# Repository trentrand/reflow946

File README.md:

# Reflow946

> **Fork notice** — This is a modified version of [Reflow946](https://github.com/DurandA/reflow946)
> by Arnaud Durand, licensed under the [Creative Commons Attribution 4.0 International
> license](LICENSE) (CC BY 4.0). See *Modifications* below for what changed.

The Reflow946 is a Bluetooth LE temperature controller for the 946C electronic hot plate. Using this controller, a reflow profile can be programmed from your web browser using the [Web Bluetooth](https://webbluetoothcg.github.io/web-bluetooth/) API. You can use preset profiles (e.g. for lead-free or leaded soldering) or create a custom profile for a perfect cheese fondue. 🫕

The controller board is intended to replace the original controller board. It is **only compatible with the 3 buttons variant** pictured above (see this [teardown](https://youtu.be/Gv2sRJ9y_Ok)). Please send a PR if you adapted the design to a new variant.

## Hardware

The controller is based on a ESP32 module with an IPEX antenna. Since the metal case acts as a Faraday cage, the BLE signal can be improved by taping an antenna outside of the case.

### Front

### Back

## Status

- [x] Temperature control
  - [x] Temperature control using the front panel
  - [x] [BLE GATT service](https://github.com/DurandA/reflow946-firmware/wiki/GATT-Services) for temperature control
- [x] Reflow profile programming
  - [x] [BLE GATT service](https://github.com/DurandA/reflow946-firmware/wiki/GATT-Services) for reflow profiles
  - [x] [Web Bluetooth application](https://duranda.github.io/reflow946/)

## Modifications

Changes by Trent Rand (Randware), relative to upstream rev 1.2:

- Pathfinder revision (rev 2): 3-digit 7-segment display (`DS1`) replaced by a
  1.47" IPS TFT (ST7789V3, 172x320) with two parallel interfaces:
  `J6` FH12-8S-0.5SH FPC connector (v2 mounting path) and `J9` 2.54mm breakout
  header (bench bring-up). Signals ride the former segment-drive GPIOs:
  BL=dp(IO5) CS=f(IO23) DC=d(IO16) RES=g(IO13) SDA=c(IO19) SCL=d2(IO18).
  One display may be attached at a time (shared bus).
- Second MAX31855KASA (`U6`) with screw terminal `J8` (`EXT_TC`) for top-of-PCB
  thermocouple profiling; shares CLK/MISO with the primary sensor, CS on IO4.
- Breakout `J7` (CLK / MISO / CS_EXT / TC_ADC / 3V3 / GND): digital probe amps
  on the shared SPI bus, or analog amplifiers (AD8495) on TC_ADC = SENSOR_VP.
- IO17/IO22 left as spare GPIOs (I2C-capable; add pull-ups with the device).

Upstream hardware errata and revision notes are preserved in [`hardware/README.md`](hardware/README.md).

## Credits

* Arnaud Durand - Original design ([CC BY 4.0](https://creativecommons.org/licenses/by/4.0/))
* Elías Rodríguez Martín - Revision 1.1, conversion to KiCad
* Trent Rand (Randware) - OLED display interface, external probe interface

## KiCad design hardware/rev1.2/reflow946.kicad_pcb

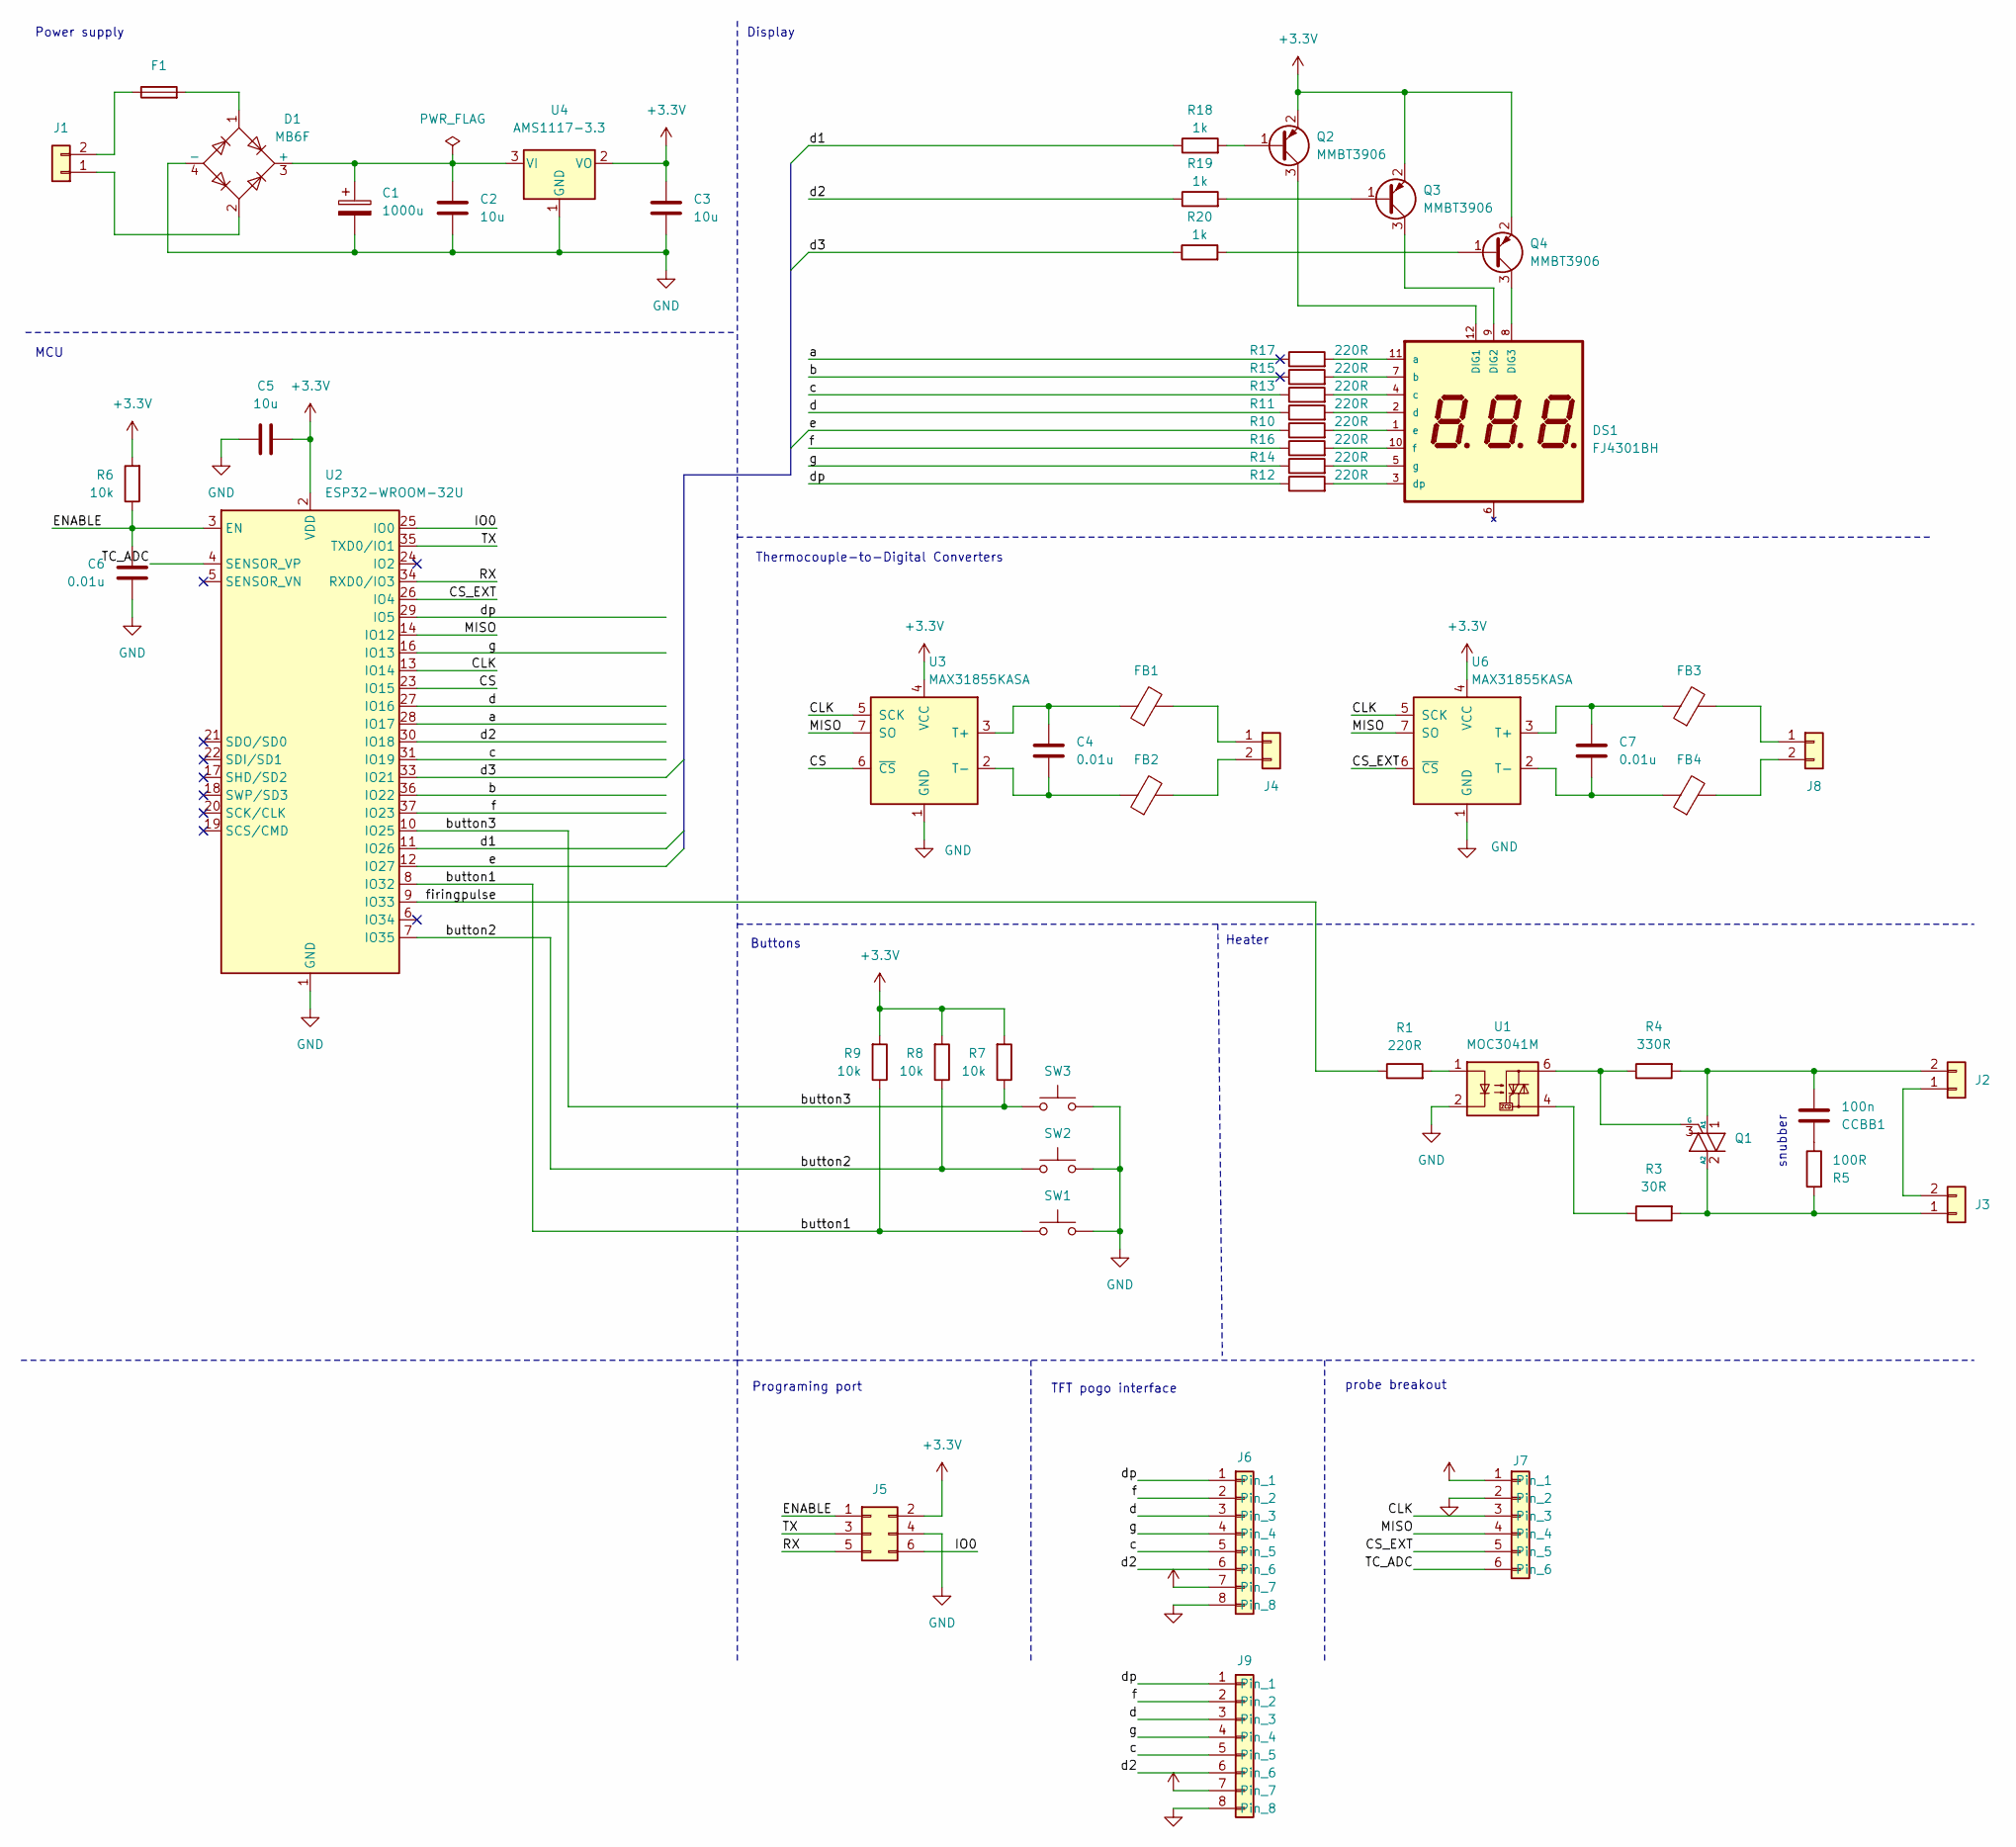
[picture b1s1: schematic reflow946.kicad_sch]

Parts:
C1: 1000u; CP_Radial_D10.0mm_P5.00mm
C2, C3, C5: 10u; C_0805_2012Metric_Pad1.18x1.45mm_HandSolder
C4, C6, C7: 0.01u; C_0805_2012Metric_Pad1.18x1.45mm_HandSolder
CCBB1: 100n; C_Rect_L13.0mm_W6.0mm_P10.00mm_FKS3_FKP3_MKS4; Part Number MP1104K44C3R6LC; LCSC Part # C105712
D1: MB6F; MB-F; Part Number MB6F; LCSC Part # C2490
DS1: FJ4301BH; Part Number C10706; LCSC Part # C10706
F1: SMD0805-020-16V; Fuse_0805_2012Metric_Pad1.15x1.40mm_HandSolder; Part Number SMD0805-020-16V; LCSC Part # C70057
FB1, FB2, FB3, FB4: FerriteBead; R_0603_1608Metric_Pad0.98x0.95mm_HandSolder
J1: VH-2A; JST_VH_B2P-VH_1x02_P3.96mm_Vertical; Part Number VH-2A; LCSC Part # C16728
J2, J3: VH-3A2; JST_VH_B2P3-VH_1x02_P7.92mm_Vertical; Part Number VH-3A2; LCSC Part # C18157
J4: XH-A2; CONN-TH_XH-2A; Part Number XH-2A; LCSC Part # C20079
J5: HDR-M-2.54_2x3; PinHeader_2x03_P2.54mm_Vertical; Part Number C65114; LCSC Part # C65114
J6: TFT_1.47; Hirose_FH12-8S-0.5SH_1x08-1MP_P0.50mm_Horizontal
J7: PROBE_BRK; PinHeader_1x06_P2.54mm_Vertical
J8: EXT_TC; TerminalBlock_Phoenix_MPT-0,5-2-2.54_1x02_P2.54mm_Horizontal; Part Number XH-2A; LCSC Part # C20079
J9: TFT_1.47; PinHeader_1x08_P2.54mm_Vertical
Q1: BTA16-600BRG; TO-220-3_Horizontal_TabUp; Part Number BTA16-600BRG; LCSC Part # C9100
Q2, Q3, Q4: MMBT3906; SOT-23; Part Number MMBT3906; LCSC Part # C181120
R1, R10, R11, R12, R13, R14, R15, R16, R17: 220R; R_0603_1608Metric_Pad0.98x0.95mm_HandSolder
R3: 30R; R_Axial_DIN0309_L9.0mm_D3.2mm_P12.70mm_Horizontal
R4: 330R; R_Axial_DIN0309_L9.0mm_D3.2mm_P12.70mm_Horizontal
R5: 100R; R_Axial_DIN0414_L11.9mm_D4.5mm_P15.24mm_Horizontal
R6, R7, R8, R9: 10k; R_0603_1608Metric_Pad0.98x0.95mm_HandSolder
R18, R19, R20: 1k; R_0603_1608Metric_Pad0.98x0.95mm_HandSolder
SW1, SW2, SW3: SW_Push; SW-TH_D6C10F1LFS; Part Number D6C40F1LFS; LCSC Part # C2689630
U1: MOC3041M; DIP-6_W7.62mm_LongPads; Part Number MOC3041M; LCSC Part # C8921
U2: ESP32-WROOM-32U; Part Number ESP32-WROOM-32U-H4; LCSC Part # C3013938
U3, U6: MAX31855KASA; SOIC-8_3.9x4.9mm_P1.27mm; Part Number MAX31855KASA+T; LCSC Part # C52028
U4: AMS1117-3.3; SOT-223-3_TabPin2; Part Number AMS1117-3.3; LCSC Part # C6186

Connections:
+3.3V: C3.1, C5.2, J5.2, J6.7, J7.1, J9.7, Q2.2 (E), Q3.2 (E), Q4.2 (E), R6.2, R7.2, R8.2, R9.2, U2.2 (VDD), U3.4 (VCC), U4.2 (VO), U6.4 (VCC)
/CLK: J7.3, U2.13 (IO14), U3.5 (SCK), U6.5 (SCK)
/CS: U2.23 (IO15), U3.6 (~CS)
/CS_EXT: J7.5, U2.26 (IO4), U6.6 (~CS)
/ENABLE: C6.2, J5.1, R6.1, U2.3 (EN)
/IO0: J5.6, U2.25 (IO0)
/MISO: J7.4, U2.14 (IO12), U3.7 (SO), U6.7 (SO)
/RX: J5.5, U2.34 (RXD0/IO3)
/TC_ADC: J7.6, U2.4 (SENSOR_VP)
/TX: J5.3, U2.35 (TXD0/IO1)
/a: R17.1, U2.28 (IO17)
/b: R15.1, U2.36 (IO22)
/button1: R9.1, SW1.1, U2.8 (IO32)
/button2: R8.1, SW2.1, U2.7 (IO35)
/button3: R7.1, SW3.1, U2.10 (IO25)
/c: J6.5, J9.5, R13.1, U2.31 (IO19)
/d: J6.3, J9.3, R11.1, U2.27 (IO16)
/d1: R18.1, U2.11 (IO26)
/d2: J6.6, J9.6, R19.1, U2.30 (IO18)
/d3: R20.1, U2.33 (IO21)
/dp: J6.1, J9.1, R12.1, U2.29 (IO5)
/e: R10.1, U2.12 (IO27)
/f: J6.2, J9.2, R16.1, U2.37 (IO23)
/firingpulse: R1.1, U2.9 (IO33)
/g: J6.4, J9.4, R14.1, U2.16 (IO13)
GND: C1.2, C2.2, C3.2, C5.1, C6.1, D1.4 (-), J5.4, J6.8, J7.2, J9.8, SW1.2, SW2.2, SW3.2, U1.2, U2.1 (GND), U2.15 (GND), U2.38 (GND), U2.39 (GND), U3.1 (GND), U4.1 (GND), U6.1 (GND)
unnamed: CCBB1.1, R5.1
unnamed: C1.1, C2.1, D1.3 (+), U4.3 (VI)
unnamed: D1.1, F1.2
unnamed: DS1.12 (DIG1), Q2.3 (C)
unnamed: DS1.9 (DIG2), Q3.3 (C)
unnamed: DS1.8 (DIG3), Q4.3 (C)
unnamed: DS1.11 (a), R17.2
unnamed: DS1.7 (b), R15.2
unnamed: DS1.4 (c), R13.2
unnamed: DS1.2 (d), R11.2
unnamed: DS1.3 (dp), R12.2
unnamed: DS1.1 (e), R10.2
unnamed: DS1.10 (f), R16.2
unnamed: DS1.5 (g), R14.2
unnamed: D1.2, J1.1
unnamed: F1.1, J1.2
unnamed: J2.1, J3.2
unnamed: CCBB1.2, J2.2, Q1.1 (A1), R4.2
unnamed: J3.1, Q1.2 (A2), R3.2, R5.2
unnamed: FB1.2, J4.1
unnamed: FB2.2, J4.2
unnamed: FB3.2, J8.1
unnamed: FB4.2, J8.2
unnamed: Q1.3 (G), R4.1, U1.6
unnamed: Q2.1 (B), R18.2
unnamed: Q3.1 (B), R19.2
unnamed: Q4.1 (B), R20.2
unnamed: R1.2, U1.1
unnamed: R3.1, U1.4
unnamed: C4.1, FB1.1, U3.3 (T+)
unnamed: C4.2, FB2.1, U3.2 (T-)
unnamed: C7.1, FB3.1, U6.3 (T+)
unnamed: C7.2, FB4.1, U6.2 (T-)

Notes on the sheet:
Power supply
Programing port
Thermocouple-to-Digital Converters
TFT pogo interface
snubber
probe breakout
MCU
Heater
Display
Buttons

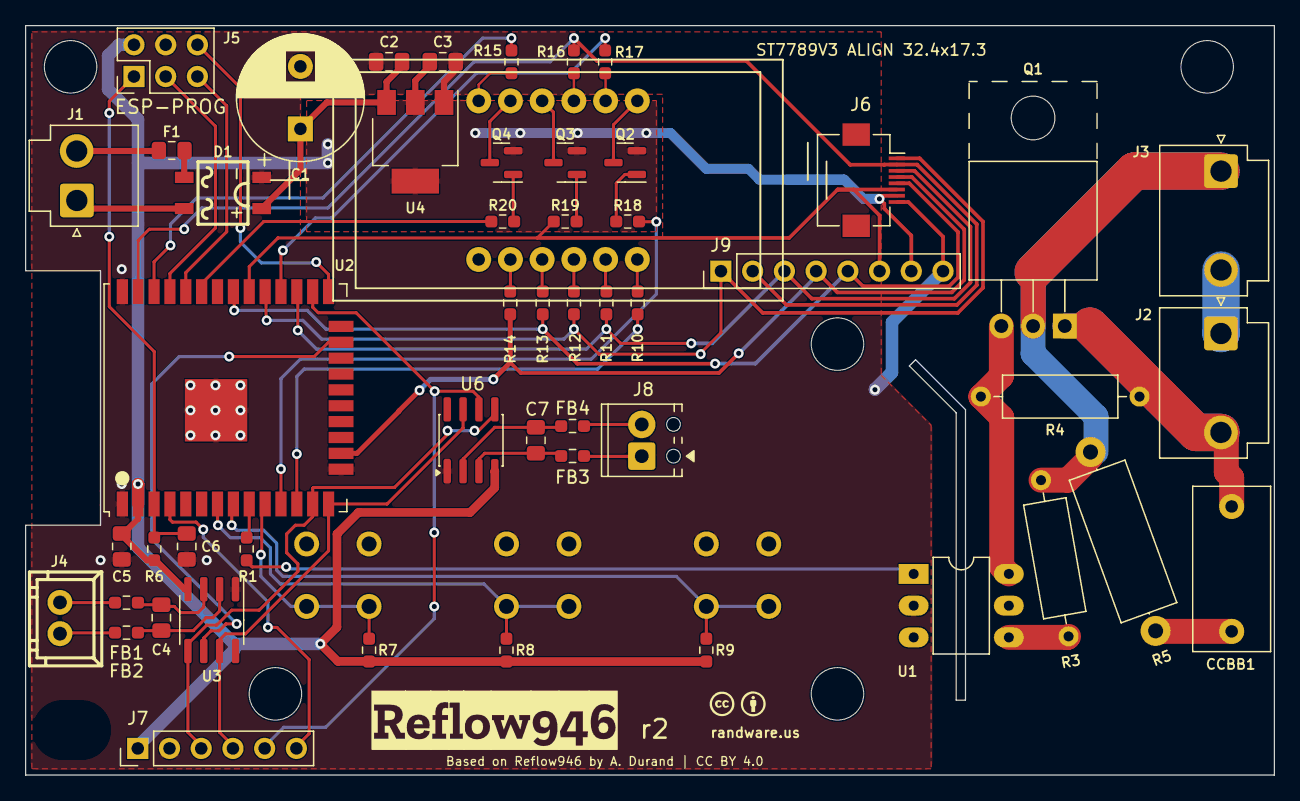
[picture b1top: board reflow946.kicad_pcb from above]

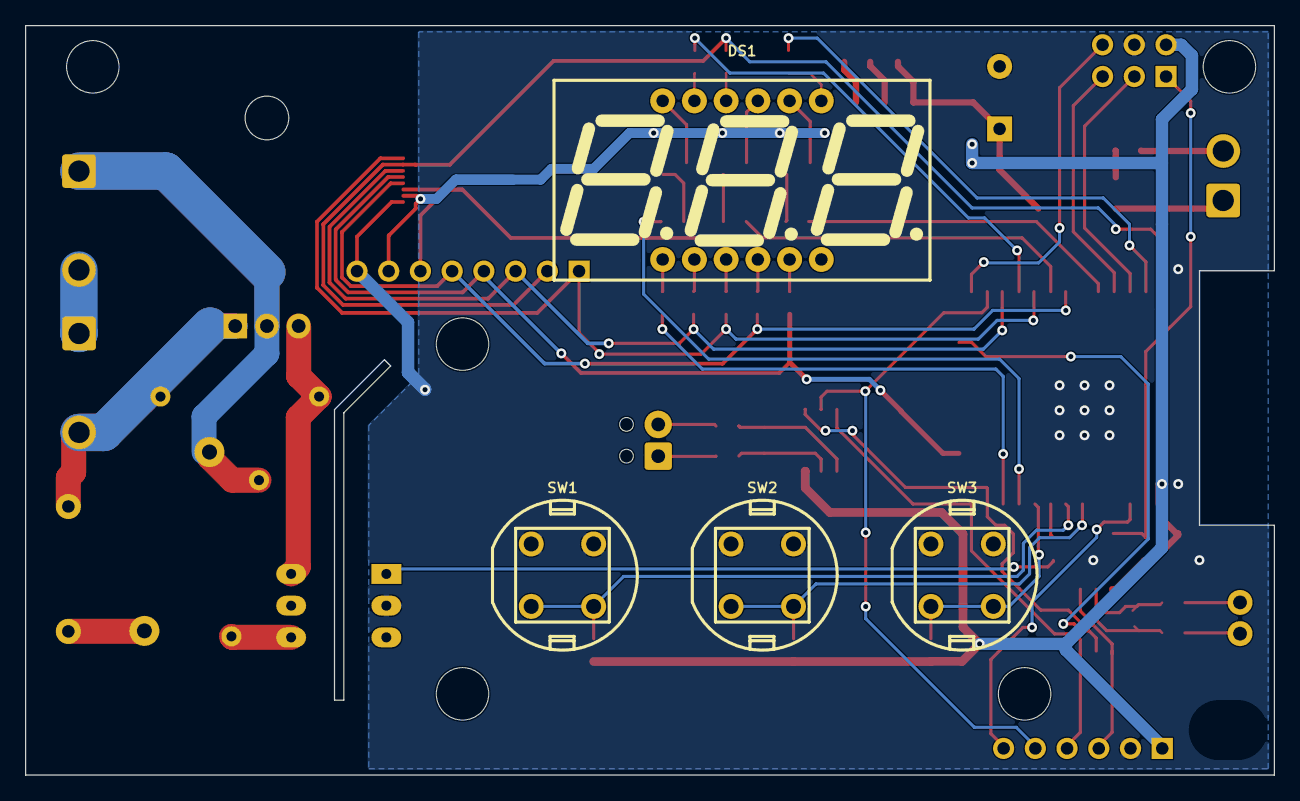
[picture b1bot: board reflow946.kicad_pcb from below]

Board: 2 copper layers, 100.0 x 60.0 mm, 56 parts (4 on the bottom side), 59 nets.

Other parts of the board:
kibuzzard-632CED8E: G***; kibuzzard-632CED8E

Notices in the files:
hardware/rev1.2/reflow946.kicad_pcb:
Based on Reflow946 by A. Durand | CC BY 4.0
